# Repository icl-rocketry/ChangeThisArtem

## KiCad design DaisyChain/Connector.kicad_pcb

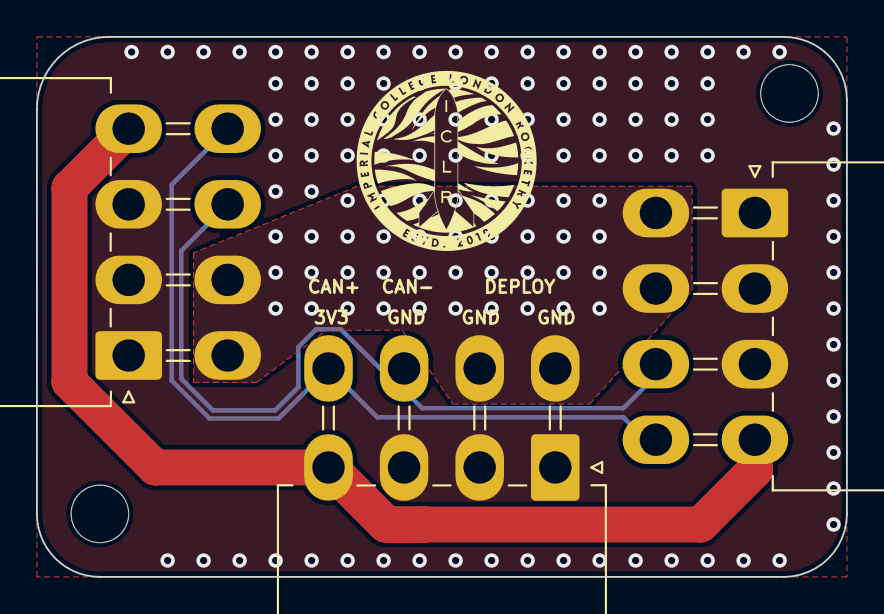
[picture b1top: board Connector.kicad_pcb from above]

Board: 2 copper layers, 45.0 x 30.0 mm, 5 parts (0 on the bottom side), 5 nets.

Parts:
H1, H2: MountingHole_Pad; MountingHole_3.2mm_M3_DIN965
J1, J2, J3: Conn_01x08_Female; Molex_Mini-Fit_Jr_5569-08A2_2x04_P4.20mm_Horizontal

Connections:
/3.3V: J1.4, J2.4, J3.4
/CAN+: J1.8, J2.8, J3.8
/CAN-: J1.7, J2.7, J3.7
/DEP+: J1.5, J1.6, J2.5, J2.6, J3.5, J3.6
GND: J1.1, J1.2, J1.3, J2.1, J2.2, J2.3, J3.1, J3.2, J3.3

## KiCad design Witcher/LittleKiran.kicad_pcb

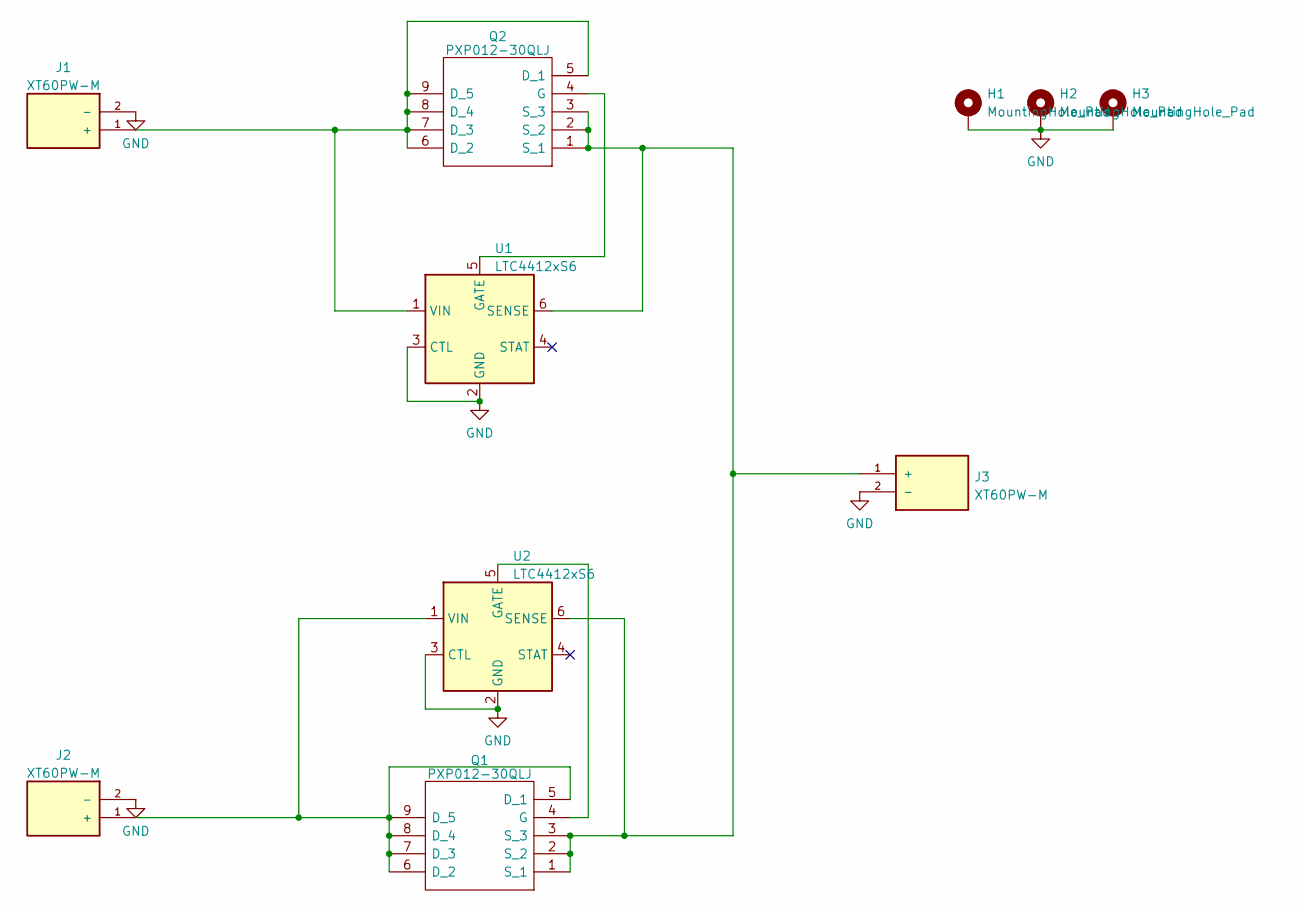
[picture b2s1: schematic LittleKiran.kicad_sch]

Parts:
H1, H2, H3: MountingHole_Pad; MountingHole_3.2mm_M3_DIN965_Pad
J1, J2, J3: XT60PW-M; AMASS_XT60PW-M; PARTREV V1.2
Q1, Q2: PXP012-30QLJ; PXP01230QLJ; Manufacturer_Part_Number PXP012-30QLJ; Mouser Part Number 771-PXP012-30QLJ
U1, U2: LTC4412xS6; TSOT-23-6

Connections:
GND: H1.1, H2.1, H3.1, J1.2 (-), J2.2 (-), J3.2 (-), U1.2 (GND), U1.3 (CTL), U2.2 (GND), U2.3 (CTL)
unnamed: J1.1 (+), Q2.5 (D_1), Q2.6 (D_2), Q2.7 (D_3), Q2.8 (D_4), Q2.9 (D_5), U1.1 (VIN)
unnamed: J2.1 (+), Q1.5 (D_1), Q1.6 (D_2), Q1.7 (D_3), Q1.8 (D_4), Q1.9 (D_5), U2.1 (VIN)
unnamed: J3.1 (+), Q1.1 (S_1), Q1.2 (S_2), Q1.3 (S_3), Q2.1 (S_1), Q2.2 (S_2), Q2.3 (S_3), U1.6 (SENSE), U2.6 (SENSE)
unnamed: Q1.4 (G), U2.5 (GATE)
unnamed: Q2.4 (G), U1.5 (GATE)

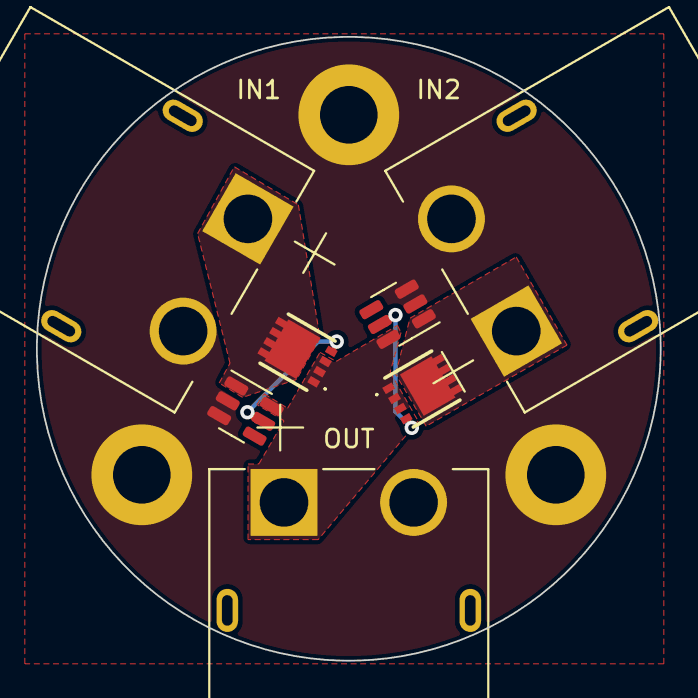
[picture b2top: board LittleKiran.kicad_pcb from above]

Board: 2 copper layers, 34.7 x 34.7 mm, 10 parts (0 on the bottom side), 6 nets.

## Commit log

2023-04-20 sorry andrei, dont know how to change the name of the repo
2023-05-16 finito
2023-05-22 splitting into 2 repos
2023-06-16 silkscreen
